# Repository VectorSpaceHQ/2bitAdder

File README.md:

# 2-bit Adder

2-bit Adder printed circuit board designed with KiCad.

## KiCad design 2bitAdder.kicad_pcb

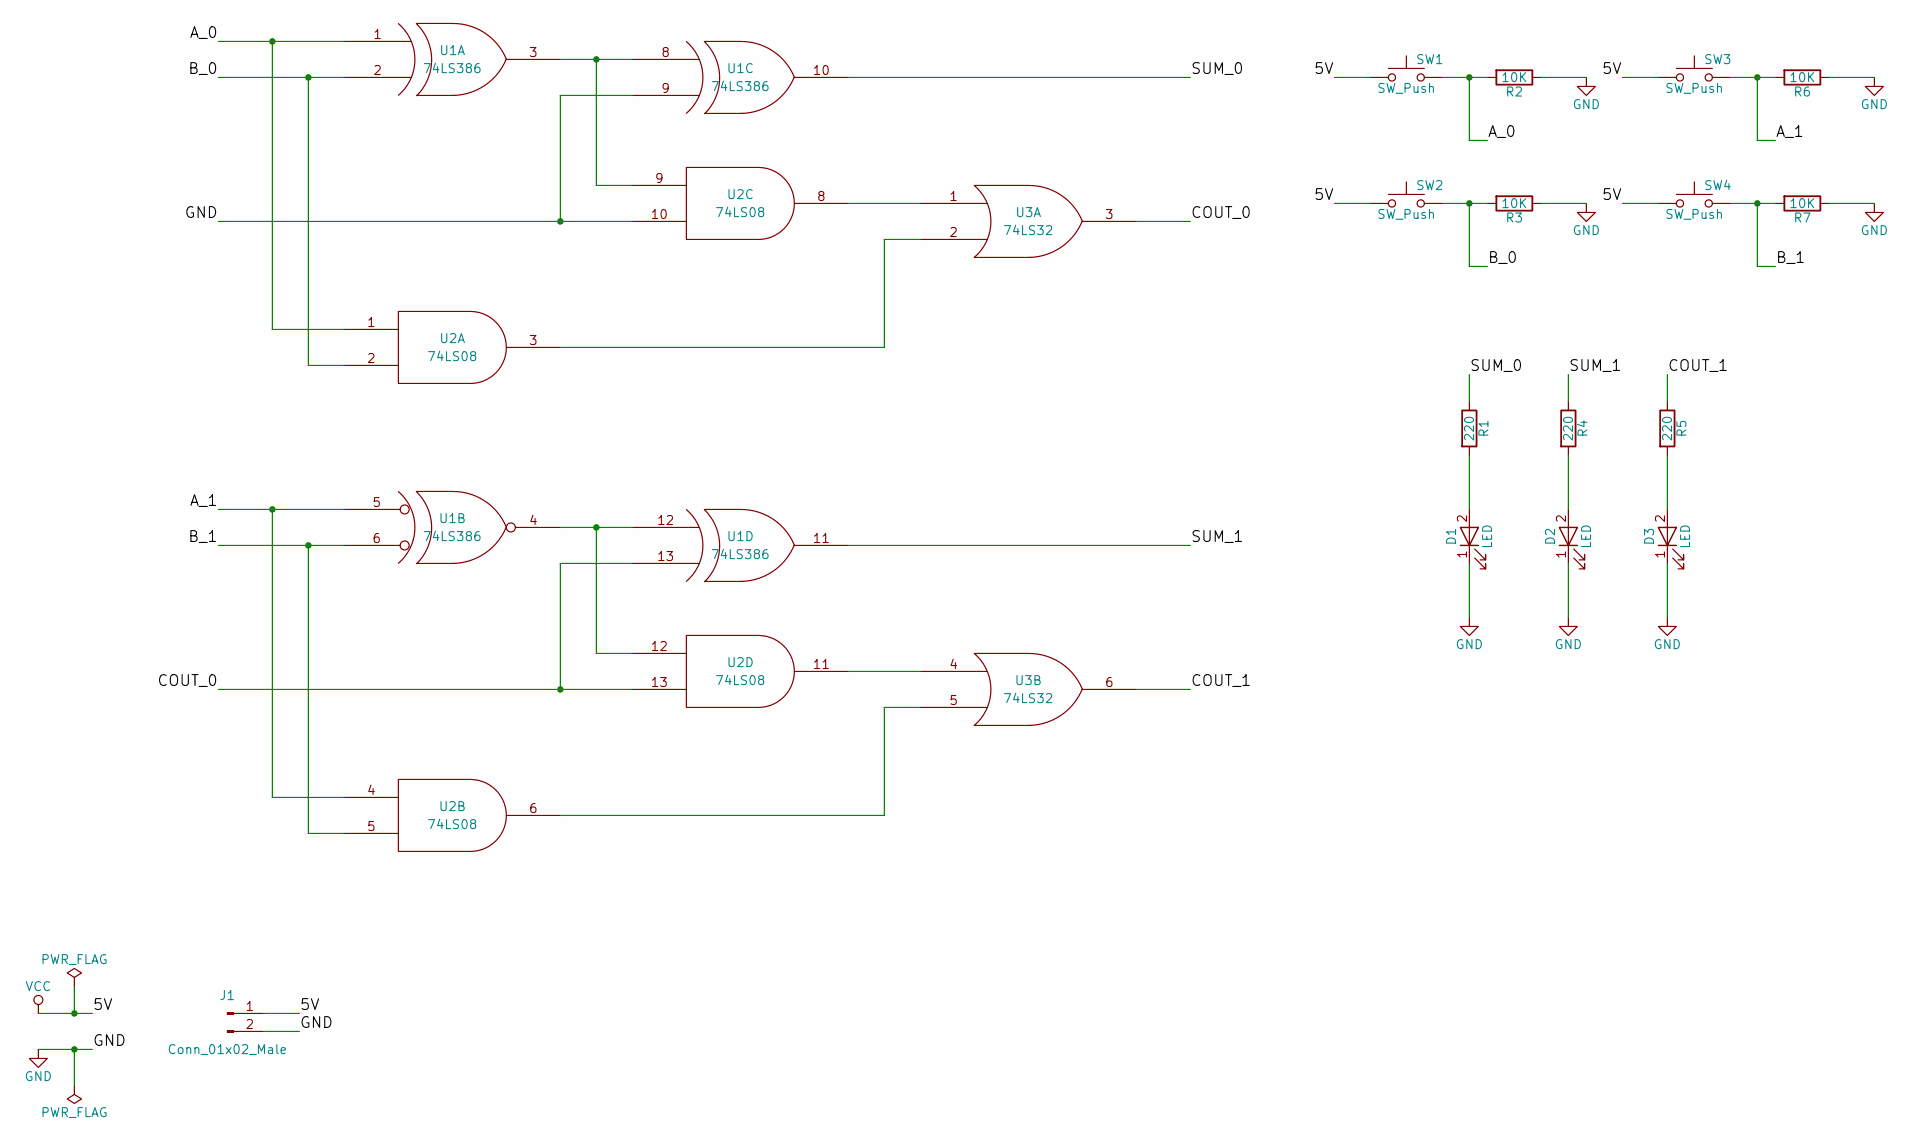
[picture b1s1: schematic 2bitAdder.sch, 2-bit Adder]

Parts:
D1, D2, D3: LED; LED_D5.0mm
J1: Conn_01x02_Male; Pin_Header_Straight_1x02_Pitch2.54mm
R1, R4, R5: 220; R_Axial_DIN0207_L6.3mm_D2.5mm_P10.16mm_Horizontal
R2, R3, R6, R7: 10K; R_Axial_DIN0207_L6.3mm_D2.5mm_P10.16mm_Horizontal
SW1, SW2, SW3, SW4: SW_Push; SW_PUSH_6mm
U1: 74LS386; DIP-14_W7.62mm_LongPads
U2: 74LS08; DIP-14_W7.62mm_LongPads
U3: 74LS32; DIP-14_W7.62mm_LongPads

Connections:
/A_0: R2.2, SW1.2, U1.1, U2.1
/A_1: R6.2, SW3.2, U1.5, U2.4
/B_0: R3.2, SW2.2, U1.2, U2.2
/B_1: R7.2, SW4.2, U1.6, U2.5
/COUT_0: U1.13, U2.13, U3.3
/COUT_1: R5.1, U3.6
/SUM_0: R1.1, U1.10
/SUM_1: R4.1, U1.11
GND: D1.1 (K), D2.1 (K), D3.1 (K), J1.2, R2.1, R3.1, R6.1, R7.1, U1.7 (GND), U1.9, U2.7 (GND), U2.10, U3.7 (GND)
unnamed: D1.2 (A), R1.2
unnamed: D2.2 (A), R4.2
unnamed: D3.2 (A), R5.2
unnamed: U1.3, U1.8, U2.9
unnamed: U1.4, U1.12, U2.12
unnamed: U2.3, U3.2
unnamed: U2.6, U3.5
unnamed: U2.8, U3.1
unnamed: U2.11, U3.4
VCC: J1.1, SW1.1, SW2.1, SW3.1, SW4.1, U1.14 (VCC), U2.14 (VCC), U3.14 (VCC)

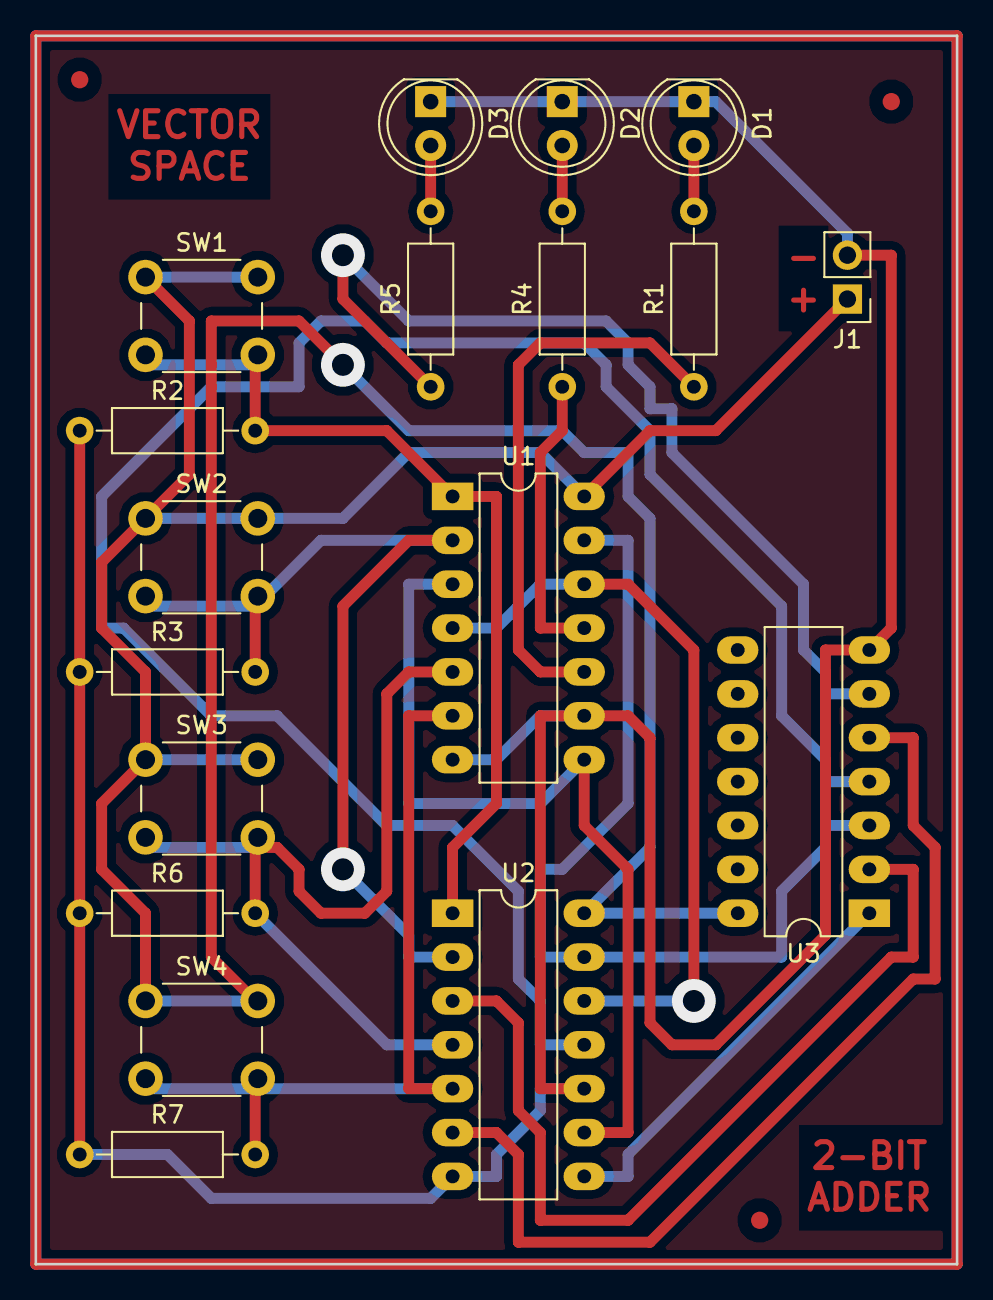
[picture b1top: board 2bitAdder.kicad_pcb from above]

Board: 2 copper layers, 53.3 x 71.1 mm, 18 parts (0 on the bottom side), 19 nets.

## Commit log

2017-11-14 Make vias bigger
2017-11-14 Add text and board outline
2017-11-14 Add fiducials to help with alignment
2017-11-14 Add board outline to Edge cuts layer
2017-11-14 Add filled zones
2017-11-14 Update netlist
2017-11-14 Add 3D Rendering of board
2017-11-14 Ignore backup files
2017-11-14 Resize 3d image
2017-11-14 Remove zip file
2017-11-14 Remove old gerbers
2017-11-14 Remove old SVG files
2017-11-14 Plot SVGs for printing
2017-11-14 Added +/- indicator to power pins
